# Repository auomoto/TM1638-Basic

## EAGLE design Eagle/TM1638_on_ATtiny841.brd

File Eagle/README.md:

Version 4 was done at OSHPark but came with one problem. Pin 14 on the
ATtiny841 (GND) was not connected to the ground plane even though it
looked like it should be. Pin 14 is correctly connected to the ground
side of the decoupling capacitor and the spider connections on the ground
plane side of the capacitor through hole are there, but it doesn't actually
connect.

Solution: run a jumper wire on the top of the board from the capacitor to
the nearby header pin that's at ground. This works.

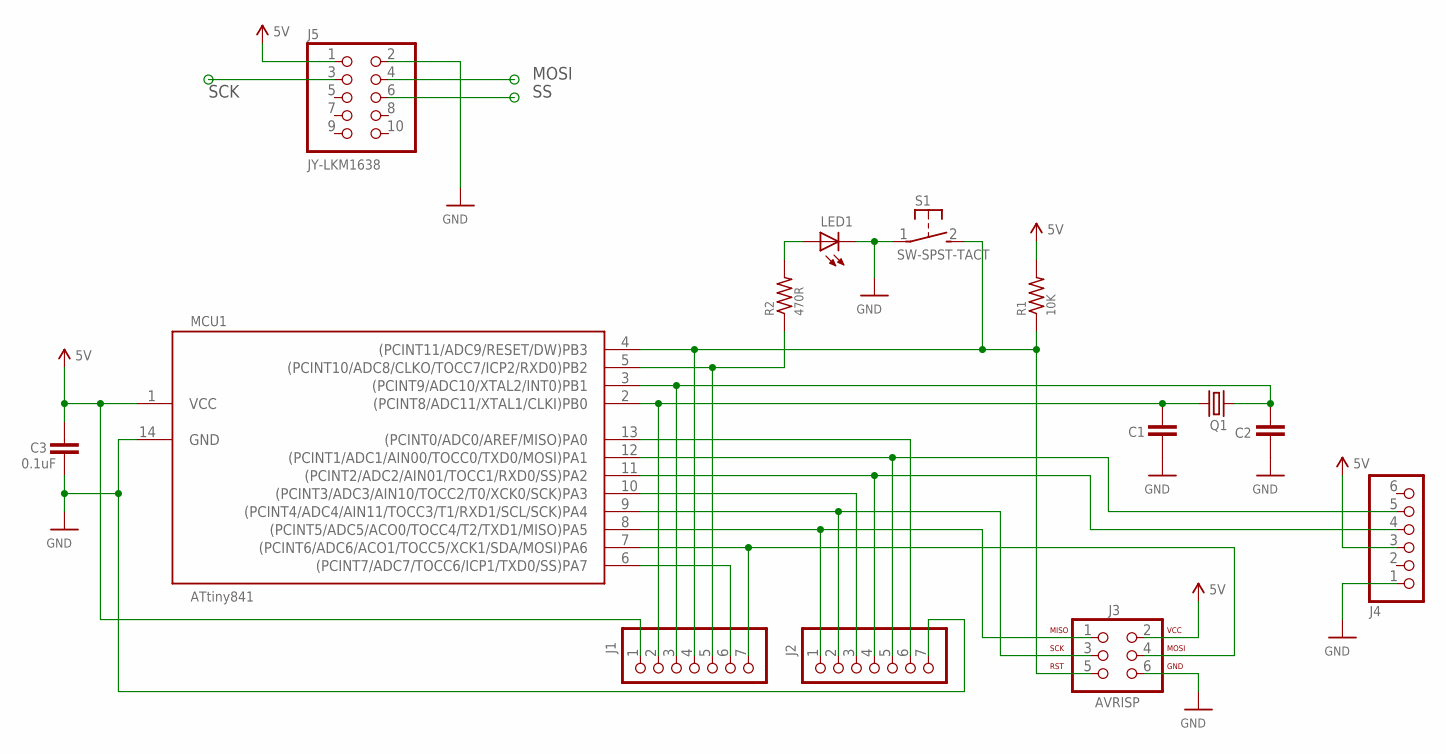
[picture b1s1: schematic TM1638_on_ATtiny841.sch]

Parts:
C1, C2: C-UNPOL; CAP-PTH-SMALL2
C3: 0.1uF; CAP-PTH-SMALL2
J1, J2: PINHD-1X71X07-CLEANBIG; 1X07-CLEANBIG
J3: AVRISP; 2X03-CLEAN
J4: PINHD-1X6CB; 1X06-CLEANBIG
J5: JY-LKM1638; 2X05
LED1: LED5MM
MCU1: ATtiny841; SOIC14
Q1: CRYSTALHC49S; HC49/S
R1: 10K; RESISTOR-0207/2V
R2: 470R; RESISTOR-0207/2V
S1: SW-SPST-TACT; DTS-3

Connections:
5V: C3.1, J1.1, J3.2, J4.3, J5.1, MCU1.1 (VCC), R1.2
GND: C1.2, C2.1, C3.2, J2.7, J3.6, J4.1, J5.2, LED1.K (C), MCU1.14 (GND), S1.1
MISO: J2.1, J3.1, MCU1.8 ((PCINT5/ADC5/ACO0/TOCC4/T2/TXD1/MISO)PA5)
MOSI: J1.7, J3.4, J5.4, MCU1.7 ((PCINT6/ADC6/ACO1/TOCC5/XCK1/SDA/MOSI)P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)
unnamed: C1.1, J1.2, MCU1.2 ((PCINT8/ADC11/XTAL1/CLKI)PB0), Q1.1
unnamed: C2.2, J1.3, MCU1.3 ((PCINT9/ADC10/XTAL2/INT0)PB1), Q1.2
unnamed: J2.6, MCU1.13 ((PCINT0/ADC0/AREF/MISO)PA0)
unnamed: J2.3, MCU1.10 ((PCINT3/ADC3/AIN10/TOCC2/T0/XCK0/SCK)PA3)
unnamed: J1.5, MCU1.5 ((PCINT10/ADC8/CLKO/TOCC7/ICP2/RXD0)PB2), R2.1
unnamed: LED1.A, R2.2
RST: J1.4, J3.5, MCU1.4 ((PCINT11/ADC9/RESET/DW)PB3), R1.1, S1.2
RTS: J2.5, J4.5, MCU1.12 ((PCINT1/ADC1/AIN00/TOCC0/TXD0/MOSI)PA1)
RXD0: J2.4, J4.4, MCU1.11 ((PCINT2/ADC2/AIN01/TOCC1/RXD0/SS)PA2)
SCK: J2.2, J3.3, J5.3, MCU1.9 ((PCINT4/ADC4/AIN11/TOCC3/T1/RXD1/SCL/SC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)
SS: J1.6, J5.6, MCU1.6 ((PCINT7/ADC7/TOCC6/ICP1/TXD0/SS)PA7)

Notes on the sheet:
SCK
MOSI

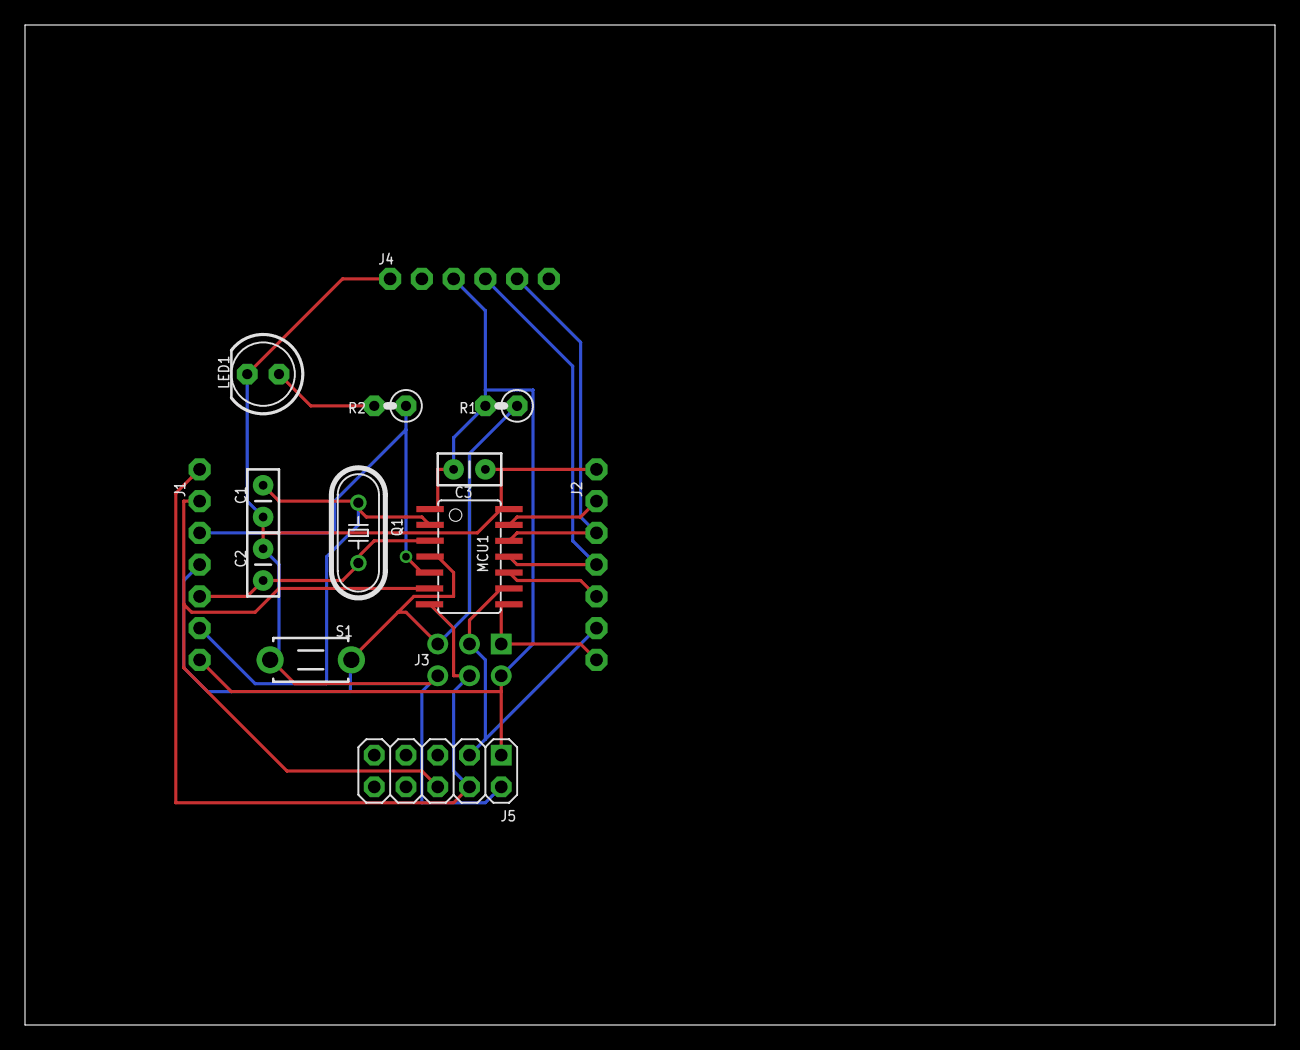
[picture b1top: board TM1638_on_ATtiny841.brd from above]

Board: 2 copper layers, 100.0 x 80.0 mm, 14 parts (0 on the bottom side), 15 nets.

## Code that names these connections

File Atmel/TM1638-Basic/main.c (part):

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=====
USART
There are two:
USART0: RXD0 is PA2 on pin 11, TXD0 is PA1 on pin 12
USART1: RXD1 is PA4 on pin 9, TXD1 is PA5 on pin 8
=====
TM1638

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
